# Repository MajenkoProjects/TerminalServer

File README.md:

Open-source Terminal Server
===========================

This is a small 6 port serial terminal server with ethernet, USB and WiFi
connectivity.

**NOTE: THIS IS WORK IN PROGRESS AND NOT COMPLETE YET**

Current status:
---------------

* **Serial Ports:** Done
* **USB Ports:** Done
* **Ethernet:** Done
* **WiFi:** Done
* **Telnet in:** Done
* **Telnet out:** Done
* **TCP in:** Done
* **TU58 Emulation:** Read/write done
* **TCP out:** Planned
* **PPP/SLIP:** Planned

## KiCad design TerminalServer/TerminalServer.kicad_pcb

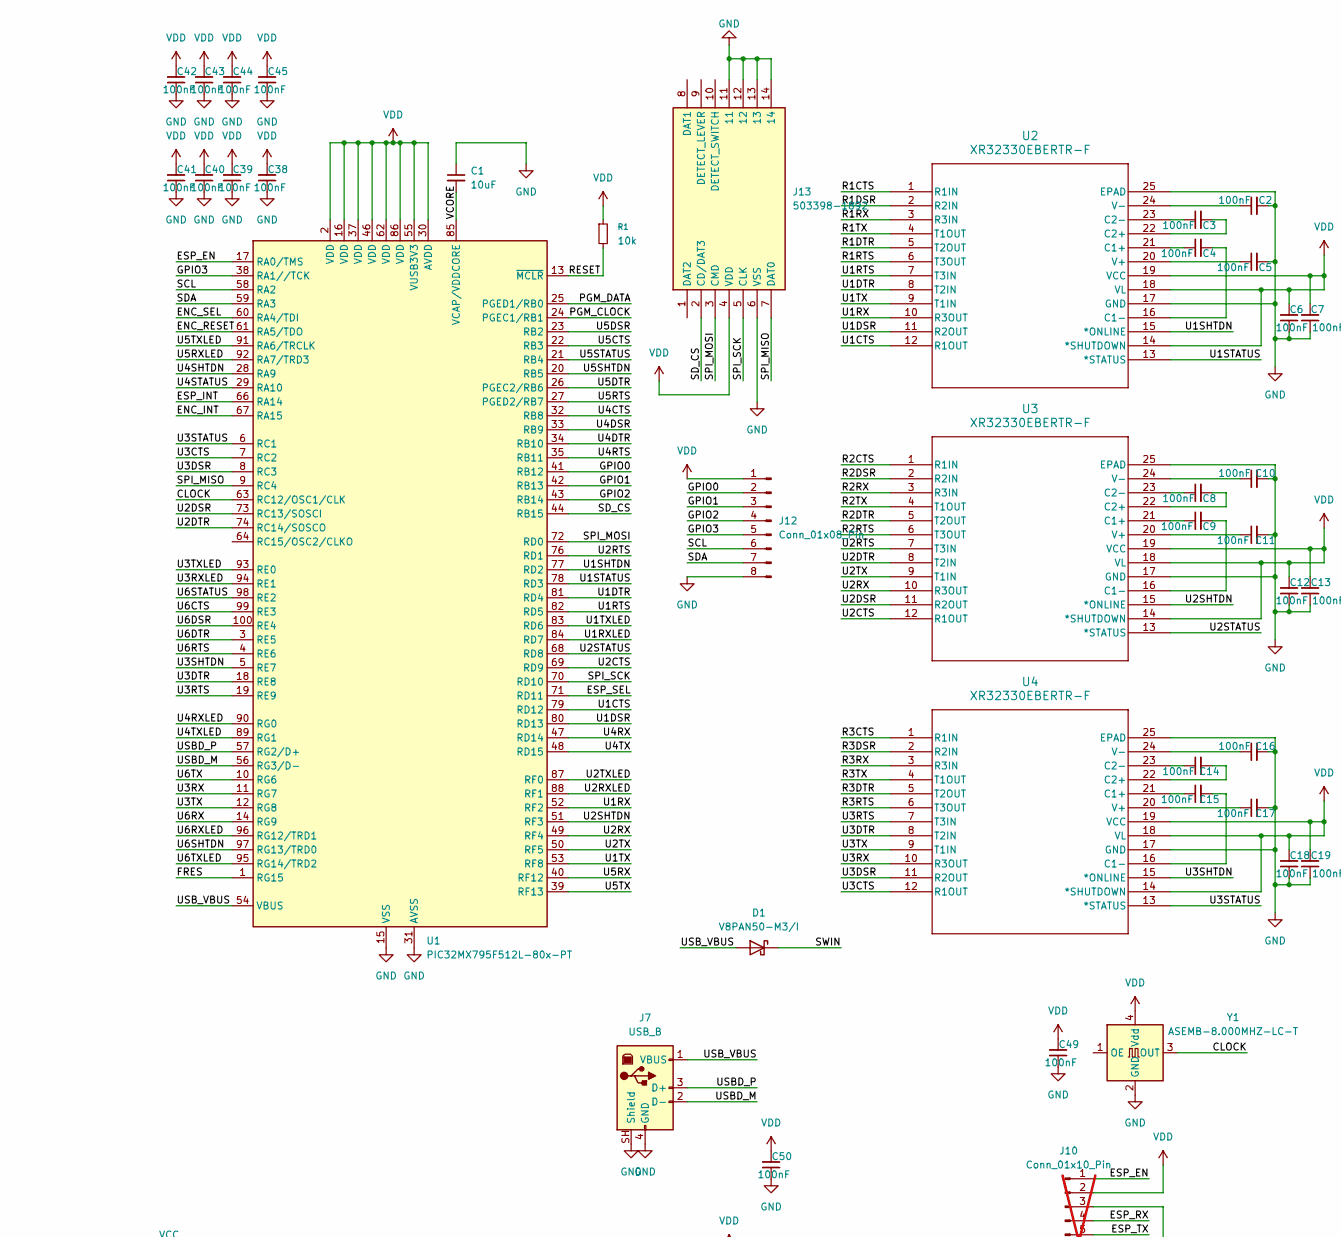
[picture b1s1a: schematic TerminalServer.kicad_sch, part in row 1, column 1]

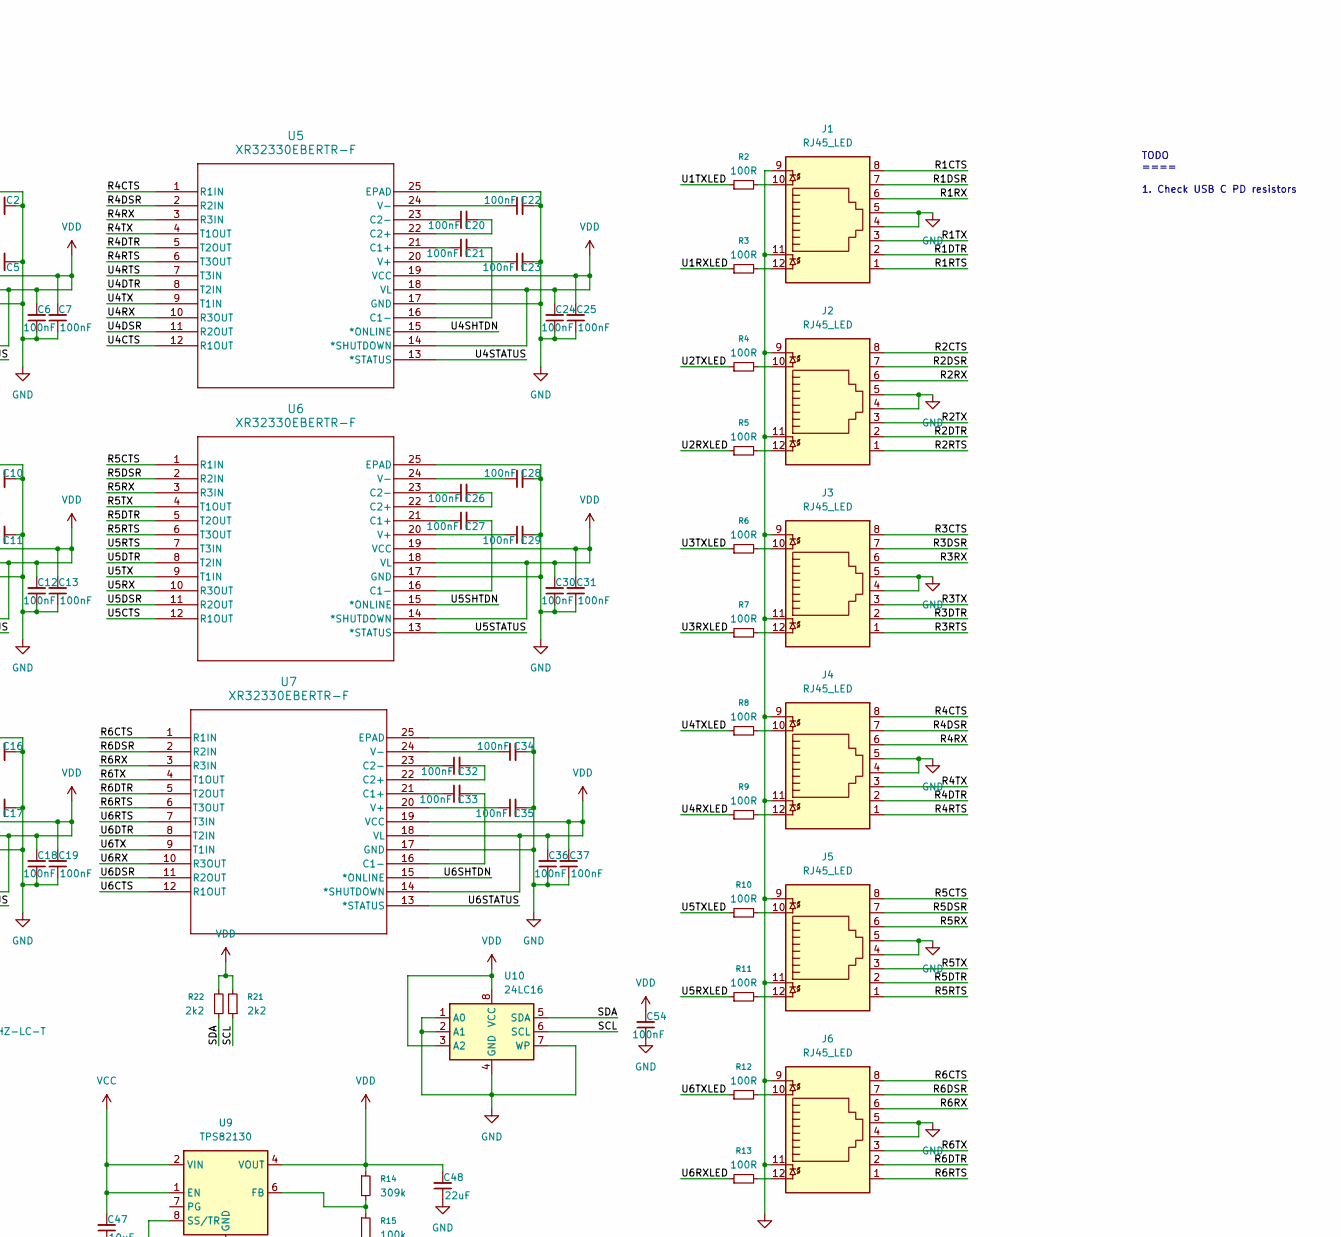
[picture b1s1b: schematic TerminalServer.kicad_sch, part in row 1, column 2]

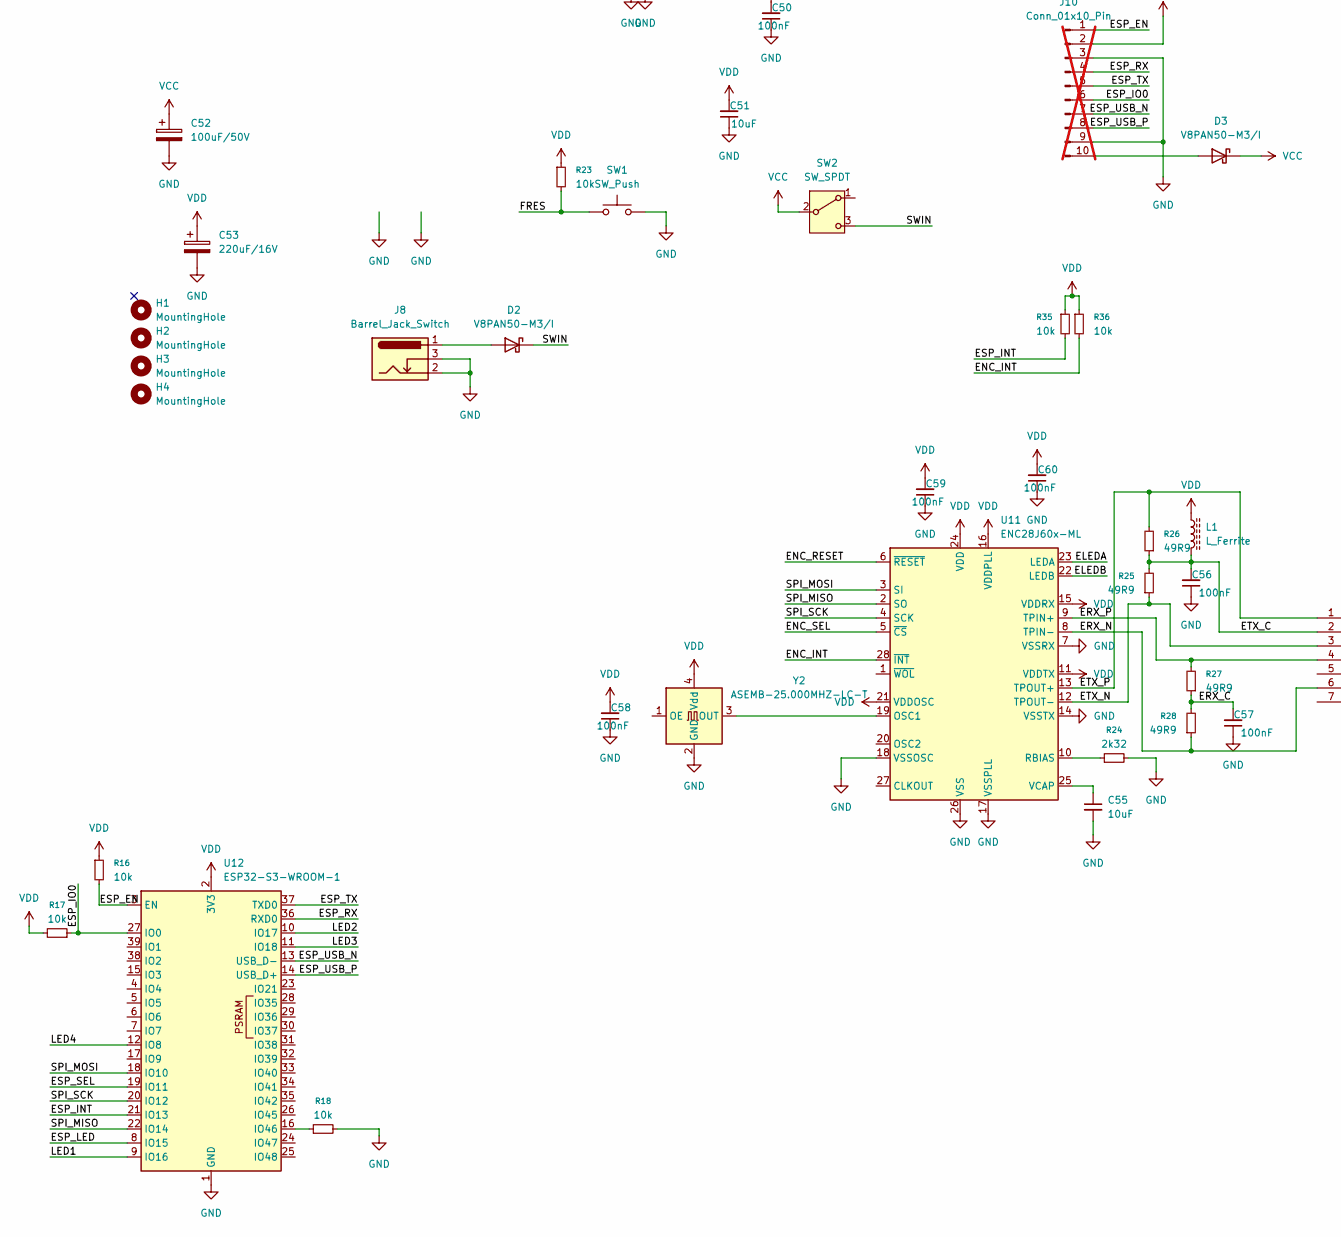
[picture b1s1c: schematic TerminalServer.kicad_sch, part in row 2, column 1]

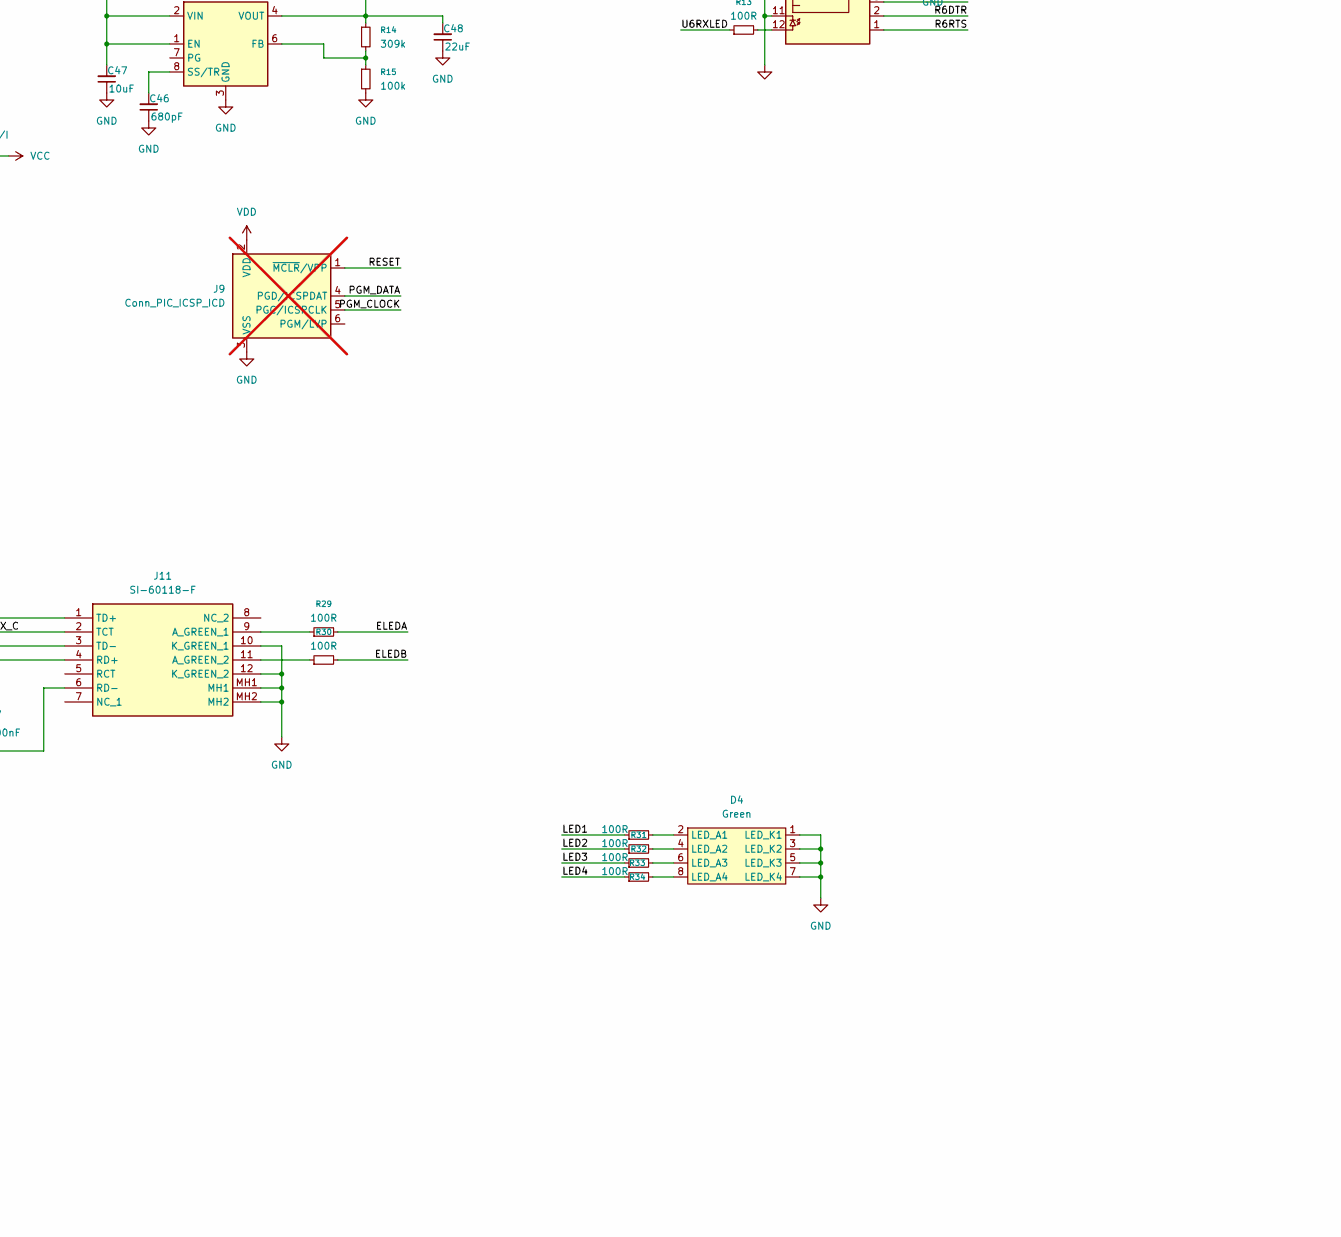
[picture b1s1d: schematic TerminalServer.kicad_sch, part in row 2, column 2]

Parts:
C1, C55: 10uF; C_0805_2012Metric_Pad1.18x1.45mm_HandSolder
C2, C3, C4, C5, C6, C7, C8, C9, C10, C11, C12, C13, C14, C15, C16, C17, C18, C19, C20, C21, C22, C23, C24, C25, C26, C27, C28, C29, C30, C31, C32, C33, C34, C35, C36, C37, C38, C39, C40, C41, C42, C43, C44, C45, C49, C50, C54, C56, C57, C58, C59, C60: 100nF; C_0603_1608Metric_Pad1.08x0.95mm_HandSolder
C46: 680pF; C_0603_1608Metric_Pad1.08x0.95mm_HandSolder
C47, C51: 10uF; C_1206_3216Metric
C48: 22uF; C_1206_3216Metric
C52: 100uF/50V; CP_Radial_D8.0mm_P3.50mm; Part ESK107M050AG3AA
C53: 220uF/16V; CP_Radial_D6.3mm_P2.50mm; Part ESK227M016AE3EA
D1, D2, D3: V8PAN50-M3/I; Vishay_SMPA; Mouser 78-V8PAN50-M3/I
D4: Green; XL-DZ234SYGD-4; Mouser 604-WP914CK4GDT
H1, H2, H3, H4: MountingHole; MountingHole_3.2mm_M3
J1, J2, J3, J4, J5, J6: RJ45_LED; RJ45_MTJ-88ARX1-LH_ADM; Mouser 737-MTJ-88ARX1-LH
J7: USB_B; USB_B_OST_USB-B1HSxx_Horizontal; Mouser 200-USBBSFBTHFR
J8: Barrel_Jack_Switch; BarrelJack_Wuerth_6941xx301002; Mouser 710-694106301002
J9: Conn_PIC_ICSP_ICD; PinHeader_1x06_P2.54mm_Vertical; not fitted
J10: Conn_01x10_Pin; PinHeader_1x10_P2.54mm_Vertical; not fitted
J11: SI-60118-F; SI60118F; Mouser Part Number 530-SI-60118-F
J12: Conn_01x08_Pin; PinHeader_1x08_P2.54mm_Vertical
J13: 503398-1892; 5033981892; Mouser Part Number 538-503398-1892
L1: L_Ferrite; L_0603_1608Metric_Pad1.05x0.95mm_HandSolder
R1, R16, R17, R18, R23, R35, R36: 10k; R_0603_1608Metric_Pad0.98x0.95mm_HandSolder
R2, R3, R4, R5, R6, R7, R8, R9, R10, R11, R12, R13, R29, R30, R31, R32, R33, R34: 100R; R_0603_1608Metric_Pad0.98x0.95mm_HandSolder
R14: 309k; R_0603_1608Metric_Pad0.98x0.95mm_HandSolder
R15: 100k; R_0603_1608Metric_Pad0.98x0.95mm_HandSolder
R21, R22: 2k2; R_0603_1608Metric_Pad0.98x0.95mm_HandSolder
R24: 2k32; R_0603_1608Metric_Pad0.98x0.95mm_HandSolder
R25, R26, R27, R28: 49R9; R_0603_1608Metric_Pad0.98x0.95mm_HandSolder
SW1: SW_Push; SW_Tactile_SPST_Angled_PTS645Vx31-2LFS
SW2: SW_SPDT; 34ASP23B4M7RT
U1: PIC32MX795F512L-80x-PT; TQFP-100_12x12mm_P0.4mm; Mouser 579-PIC32MX795F512
U2, U3, U4, U5, U6, U7: XR32330EBERTR-F; QFN-24; Mouser 701-XR32330EBERTR-F
U9: TPS82130; Texas_SIL0008D_MicroSiP-8-1EP_2.8x3mm_P0.65mm_EP1.1x1.9mm_T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
U10: 24LC16; SOIC-8_3.9x4.9mm_P1.27mm
U11: ENC28J60x-ML; QFN-28-1EP_6x6mm_P0.65mm_EP4.25x4.25mm
U12: ESP32-S3-WROOM-1
Y1: ASEMB-8.000MHZ-LC-T; Oscillator_SMD_SiT_PQFN-4Pin_3.2x2.5mm
Y2: ASEMB-25.000MHZ-LC-T; Oscillator_SMD_SiT_PQFN-4Pin_3.2x2.5mm

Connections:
/CLOCK: U1.63 (RC12/OSC1/CLK), Y1.3 (OUT)
/ELEDA: R29.2, U11.23 (LEDA)
/ELEDB: R30.2, U11.22 (LEDB)
/ENC_INT: R36.2, U1.67 (RA15), U11.28 (~INT)
/ENC_RESET: U1.61 (RA5/TDO), U11.6 (~RESET)
/ENC_SEL: U1.60 (RA4/TDI), U11.5 (~CS)
/ERX_C: C57.2, R27.1, R28.2
/ERX_N: J11.6 (RD-), R28.1, U11.8 (TPIN-)
/ERX_P: J11.4 (RD+), R27.2, U11.9 (TPIN+)
/ESP_EN: J10.1, R16.2, U1.17 (RA0/TMS), U12.3 (EN)
/ESP_INT: R35.2, U1.66 (RA14), U12.21 (IO13)
/ESP_IO0: J10.6, R17.1, U12.27 (IO0)
/ESP_LED: U12.8 (IO15)
/ESP_RX: J10.4, U12.36 (RXD0)
/ESP_SEL: U1.71 (RD11), U12.19 (IO11)
/ESP_TX: J10.5, U12.37 (TXD0)
/ESP_USB_N: J10.7, U12.13 (USB_D-)
/ESP_USB_P: J10.8, U12.14 (USB_D+)
/ETX_C: C56.2, J11.2 (TCT), L1.2, R25.2, R26.1
/ETX_N: J11.3 (TD-), R25.1, U11.12 (TPOUT-)
/ETX_P: J11.1 (TD+), R26.2, U11.13 (TPOUT+)
/FRES: R23.2, SW1.1, U1.1 (RG15)
/GPIO0: J12.2, U1.41 (RB12)
/GPIO1: J12.3, U1.42 (RB13)
/GPIO2: J12.4, U1.43 (RB14)
/GPIO3: J12.5, U1.38 (RA1//TCK)
/LED1: R31.1, U12.9 (IO16)
/LED2: R32.1, U12.10 (IO17)
/LED3: R33.1, U12.11 (IO18)
/LED4: R34.1, U12.12 (IO8)
/PGM_CLOCK: J9.5 (PGC/ICSPCLK), U1.24 (PGEC1/RB1)
/PGM_DATA: J9.4 (PGD/ICSPDAT), U1.25 (PGED1/RB0)
/R1CTS: J1.8, U2.1 (R1IN)
/R1DSR: J1.7, U2.2 (R2IN)
/R1DTR: J1.2, U2.5 (T2OUT)
/R1RTS: J1.1, U2.6 (T3OUT)
/R1RX: J1.6, U2.3 (R3IN)
/R1TX: J1.3, U2.4 (T1OUT)
/R2CTS: J2.8, U3.1 (R1IN)
/R2DSR: J2.7, U3.2 (R2IN)
/R2DTR: J2.2, U3.5 (T2OUT)
/R2RTS: J2.1, U3.6 (T3OUT)
/R2RX: J2.6, U3.3 (R3IN)
/R2TX: J2.3, U3.4 (T1OUT)
/R3CTS: J3.8, U4.1 (R1IN)
/R3DSR: J3.7, U4.2 (R2IN)
/R3DTR: J3.2, U4.5 (T2OUT)
/R3RTS: J3.1, U4.6 (T3OUT)
/R3RX: J3.6, U4.3 (R3IN)
/R3TX: J3.3, U4.4 (T1OUT)
/R4CTS: J4.8, U5.1 (R1IN)
/R4DSR: J4.7, U5.2 (R2IN)
/R4DTR: J4.2, U5.5 (T2OUT)
/R4RTS: J4.1, U5.6 (T3OUT)
/R4RX: J4.6, U5.3 (R3IN)
/R4TX: J4.3, U5.4 (T1OUT)
/R5CTS: J5.8, U6.1 (R1IN)
/R5DSR: J5.7, U6.2 (R2IN)
/R5DTR: J5.2, U6.5 (T2OUT)
/R5RTS: J5.1, U6.6 (T3OUT)
/R5RX: J5.6, U6.3 (R3IN)
/R5TX: J5.3, U6.4 (T1OUT)
/R6CTS: J6.8, U7.1 (R1IN)
/R6DSR: J6.7, U7.2 (R2IN)
/R6DTR: J6.2, U7.5 (T2OUT)
/R6RTS: J6.1, U7.6 (T3OUT)
/R6RX: J6.6, U7.3 (R3IN)
/R6TX: J6.3, U7.4 (T1OUT)
/RESET: J9.1 (~MCLR/VPP), R1.2, U1.13 (~MCLR)
/SCL: J12.6, R21.1, U1.58 (RA2), U10.6 (SCL)
/SDA: J12.7, R22.1, U1.59 (RA3), U10.5 (SDA)
/SD_CS: J13.2 (CD/DAT3), U1.44 (RB15)
/SPI_MISO: J13.7 (DAT0), U1.9 (RC4), U11.2 (SO), U12.22 (IO14)
/SPI_MOSI: J13.3 (CMD), U1.72 (RD0), U11.3 (SI), U12.18 (IO10)
/SPI_SCK: J13.5 (CLK), U1.70 (RD10), U11.4 (SCK), U12.20 (IO12)
/SWIN: D1.1 (K), D2.1 (K), SW2.3 (C)
/U1CTS: U1.79 (RD12), U2.12 (R1OUT)
/U1DSR: U1.80 (RD13), U2.11 (R2OUT)
/U1DTR: U1.81 (RD4), U2.8 (T2IN)
/U1RTS: U1.82 (RD5), U2.7 (T3IN)
/U1RX: U1.52 (RF2), U2.10 (R3OUT)
/U1RXLED: R3.1, U1.84 (RD7)
/U1SHTDN: U1.77 (RD2), U2.15 (*ONLINE)
/U1STATUS: U1.78 (RD3), U2.13 (*STATUS)
/U1TX: U1.53 (RF8), U2.9 (T1IN)
/U1TXLED: R2.1, U1.83 (RD6)
/U2CTS: U1.69 (RD9), U3.12 (R1OUT)
/U2DSR: U1.73 (RC13/SOSCI), U3.11 (R2OUT)
/U2DTR: U1.74 (RC14/SOSCO), U3.8 (T2IN)
/U2RTS: U1.76 (RD1), U3.7 (T3IN)
/U2RX: U1.49 (RF4), U3.10 (R3OUT)
/U2RXLED: R5.1, U1.88 (RF1)
/U2SHTDN: U1.51 (RF3), U3.15 (*ONLINE)
/U2STATUS: U1.68 (RD8), U3.13 (*STATUS)
/U2TX: U1.50 (RF5), U3.9 (T1IN)
/U2TXLED: R4.1, U1.87 (RF0)
/U3CTS: U1.7 (RC2), U4.12 (R1OUT)
/U3DSR: U1.8 (RC3), U4.11 (R2OUT)
/U3DTR: U1.18 (RE8), U4.8 (T2IN)
/U3RTS: U1.19 (RE9), U4.7 (T3IN)
/U3RX: U1.11 (RG7), U4.10 (R3OUT)
/U3RXLED: R7.1, U1.94 (RE1)
/U3SHTDN: U1.5 (RE7), U4.15 (*ONLINE)
/U3STATUS: U1.6 (RC1), U4.13 (*STATUS)
/U3TX: U1.12 (RG8), U4.9 (T1IN)
/U3TXLED: R6.1, U1.93 (RE0)
/U4CTS: U1.32 (RB8), U5.12 (R1OUT)
/U4DSR: U1.33 (RB9), U5.11 (R2OUT)
/U4DTR: U1.34 (RB10), U5.8 (T2IN)
/U4RTS: U1.35 (RB11), U5.7 (T3IN)
/U4RX: U1.47 (RD14), U5.10 (R3OUT)
/U4RXLED: R9.1, U1.90 (RG0)
/U4SHTDN: U1.28 (RA9), U5.15 (*ONLINE)
/U4STATUS: U1.29 (RA10), U5.13 (*STATUS)
/U4TX: U1.48 (RD15), U5.9 (T1IN)
/U4TXLED: R8.1, U1.89 (RG1)
/U5CTS: U1.22 (RB3), U6.12 (R1OUT)
/U5DSR: U1.23 (RB2), U6.11 (R2OUT)
/U5DTR: U1.26 (PGEC2/RB6), U6.8 (T2IN)
/U5RTS: U1.27 (PGED2/RB7), U6.7 (T3IN)
/U5RX: U1.40 (RF12), U6.10 (R3OUT)
/U5RXLED: R11.1, U1.92 (RA7/TRD3)
/U5SHTDN: U1.20 (RB5), U6.15 (*ONLINE)
/U5STATUS: U1.21 (RB4), U6.13 (*STATUS)
/U5TX: U1.39 (RF13), U6.9 (T1IN)
/U5TXLED: R10.1, U1.91 (RA6/TRCLK)
/U6CTS: U1.99 (RE3), U7.12 (R1OUT)
/U6DSR: U1.100 (RE4), U7.11 (R2OUT)
/U6DTR: U1.3 (RE5), U7.8 (T2IN)
/U6RTS: U1.4 (RE6), U7.7 (T3IN)
/U6RX: U1.14 (RG9), U7.10 (R3OUT)
/U6RXLED: R13.1, U1.96 (RG12/TRD1)
/U6SHTDN: U1.97 (RG13/TRD0), U7.15 (*ONLINE)
/U6STATUS: U1.98 (RE2), U7.13 (*STATUS)
/U6TX: U1.10 (RG6), U7.9 (T1IN)
/U6TXLED: R12.1, U1.95 (RG14/TRD2)
/USBD_M: J7.2 (D-), U1.56 (RG3/D-)
/USBD_P: J7.3 (D+), U1.57 (RG2/D+)
/USB_VBUS: D1.2 (A), J7.1 (VBUS), U1.54 (VBUS)
/VCORE: C1.2, U1.85 (VCAP/VDDCORE)
GND: C1.1, C2.2, C5.2, C6.1, C7.1, C10.2, C11.2, C12.1, C13.1, C16.2, C17.2, C18.1, C19.1, C22.2, C23.2, C24.1, C25.1, C28.2, C29.2, C30.1, C31.1, C34.2, C35.2, C36.1, C37.1, C38.1, C39.1, C40.1, C41.1, C42.1, C43.1, C44.1, C45.1, C46.1, C47.1, C48.1, C49.1, C50.1, C51.1, C52.2, C53.2, C54.1, C55.2, C56.1, C57.1, C58.1, C59.1, C60.1, D4.1 (LED_K1), D4.3 (LED_K2), D4.5 (LED_K3), D4.7 (LED_K4), J1.4, J1.5, J1.9, J1.11, J2.4, J2.5, J2.9, J2.11, J3.4, J3.5, J3.9, J3.11, J4.4, J4.5, J4.9, J4.11, J5.4, J5.5, J5.9, J5.11, J6.4, J6.5, J6.9, J6.11, J7.4 (GND), J7.SH (Shield), J8.2, J8.3, J9.3 (VSS), J10.3, J10.9, J11.10 (K_GREEN_1), J11.12 (K_GREEN_2), J11.MH1, J11.MH2, J12.8, J13.6 (VSS), J13.11, J13.12, J13.13, J13.14, R15.2, R18.2, R24.2, SW1.2, U1.15 (VSS), U1.31 (AVSS), U1.36 (VSS), U1.45 (VSS), U1.65 (VSS), U1.75 (VSS), U2.17 (GND), U2.25 (EPAD), U3.17 (GND), U3.25 (EPAD), U4.17 (GND), U4.25 (EPAD), U5.17 (GND), U5.25 (EPAD), U6.17 (GND), U6.25 (EPAD), U7.17 (GND), U7.25 (EPAD), U9.3 (GND), U9.9 (GND), U10.1 (A0), U10.2 (A1), U10.4 (GND), U10.7 (WP), U11.7 (VSSRX), U11.14 (VSSTX), U11.17 (VSSPLL), U11.18 (VSSOSC), U11.26 (VSS), U12.1 (GND), U12.40 (GND), U12.41 (GND), Y1.2 (GND), Y2.2 (GND)
unnamed: D2.2 (A), J8.1
unnamed: D3.2 (A), J10.10
unnamed: D4.2 (LED_A1), R31.2
unnamed: D4.4 (LED_A2), R32.2
unnamed: D4.6 (LED_A3), R33.2
unnamed: D4.8 (LED_A4), R34.2
unnamed: J1.10, R2.2
unnamed: J1.12, R3.2
unnamed: J2.10, R4.2
unnamed: J2.12, R5.2
unnamed: J3.10, R6.2
unnamed: J3.12, R7.2
unnamed: J4.10, R8.2
unnamed: J4.12, R9.2
unnamed: J5.10, R10.2
unnamed: J5.12, R11.2
unnamed: J6.10, R12.2
unnamed: J6.12, R13.2
unnamed: J11.9 (A_GREEN_1), R29.1
unnamed: J11.11 (A_GREEN_2), R30.1
unnamed: C4.1, U2.21 (C1+)
unnamed: C4.2, U2.16 (C1-)
unnamed: C3.2, U2.22 (C2+)
unnamed: C3.1, U2.23 (C2-)
unnamed: C5.1, U2.20 (V+)
unnamed: C2.1, U2.24 (V-)
unnamed: C9.1, U3.21 (C1+)
unnamed: C9.2, U3.16 (C1-)
unnamed: C8.2, U3.22 (C2+)
unnamed: C8.1, U3.23 (C2-)
unnamed: C11.1, U3.20 (V+)
unnamed: C10.1, U3.24 (V-)
unnamed: C15.1, U4.21 (C1+)
unnamed: C15.2, U4.16 (C1-)
unnamed: C14.2, U4.22 (C2+)
unnamed: C14.1, U4.23 (C2-)
unnamed: C17.1, U4.20 (V+)
unnamed: C16.1, U4.24 (V-)
unnamed: C21.1, U5.21 (C1+)
unnamed: C21.2, U5.16 (C1-)
unnamed: C20.2, U5.22 (C2+)
unnamed: C20.1, U5.23 (C2-)
unnamed: C23.1, U5.20 (V+)
unnamed: C22.1, U5.24 (V-)
unnamed: C27.1, U6.21 (C1+)
unnamed: C27.2, U6.16 (C1-)
unnamed: C26.2, U6.22 (C2+)
unnamed: C26.1, U6.23 (C2-)
unnamed: C29.1, U6.20 (V+)
unnamed: C28.1, U6.24 (V-)
unnamed: C33.1, U7.21 (C1+)
unnamed: C33.2, U7.16 (C1-)
unnamed: C32.2, U7.22 (C2+)
unnamed: C32.1, U7.23 (C2-)
unnamed: C35.1, U7.20 (V+)
unnamed: C34.1, U7.24 (V-)
unnamed: R14.2, R15.1, U9.6 (FB)
unnamed: C46.2, U9.8 (SS/TR)
unnamed: U11.19 (OSC1), Y2.3 (OUT)
unnamed: R24.1, U11.10 (RBIAS)
unnamed: C55.1, U11.25 (VCAP)
unnamed: R18.1, U12.16 (IO46)
VCC: C47.2, C52.1, D3.1 (K), SW2.2 (B), U9.1 (EN), U9.2 (VIN)
VDD: C6.2, C7.2, C12.2, C13.2, C18.2, C19.2, C24.2, C25.2, C30.2, C31.2, C36.2, C37.2, C38.2, C39.2, C40.2, C41.2, C42.2, C43.2, C44.2, C45.2, C48.2, C49.2, C50.2, C51.2, C53.1, C54.2, C58.2, C59.2, C60.2, J9.2 (VDD), J10.2, J12.1, J13.4 (VDD), L1.1, R1.1, R14.1, R16.1, R17.2, R21.2, R22.2, R23.1, R35.1, R36.1, U1.2 (VDD), U1.16 (VDD), U1.30 (AVDD), U1.37 (VDD), U1.46 (VDD), U1.55 (VUSB3V3), U1.62 (VDD), U1.86 (VDD), U2.14 (*SHUTDOWN), U2.18 (VL), U2.19 (VCC), U3.14 (*SHUTDOWN), U3.18 (VL), U3.19 (VCC), U4.14 (*SHUTDOWN), U4.18 (VL), U4.19 (VCC), U5.14 (*SHUTDOWN), U5.18 (VL), U5.19 (VCC), U6.14 (*SHUTDOWN), U6.18 (VL), U6.19 (VCC), U7.14 (*SHUTDOWN), U7.18 (VL), U7.19 (VCC), U9.4 (VOUT), U9.5 (VOUT), U10.3 (A2), U10.8 (VCC), U11.11 (VDDTX), U11.15 (VDDRX), U11.16 (VDDPLL), U11.21 (VDDOSC), U11.24 (VDD), U12.2 (3V3), Y1.4 (Vdd), Y2.4 (Vdd)

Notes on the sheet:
TODO ==== 1. Check USB C PD resistors

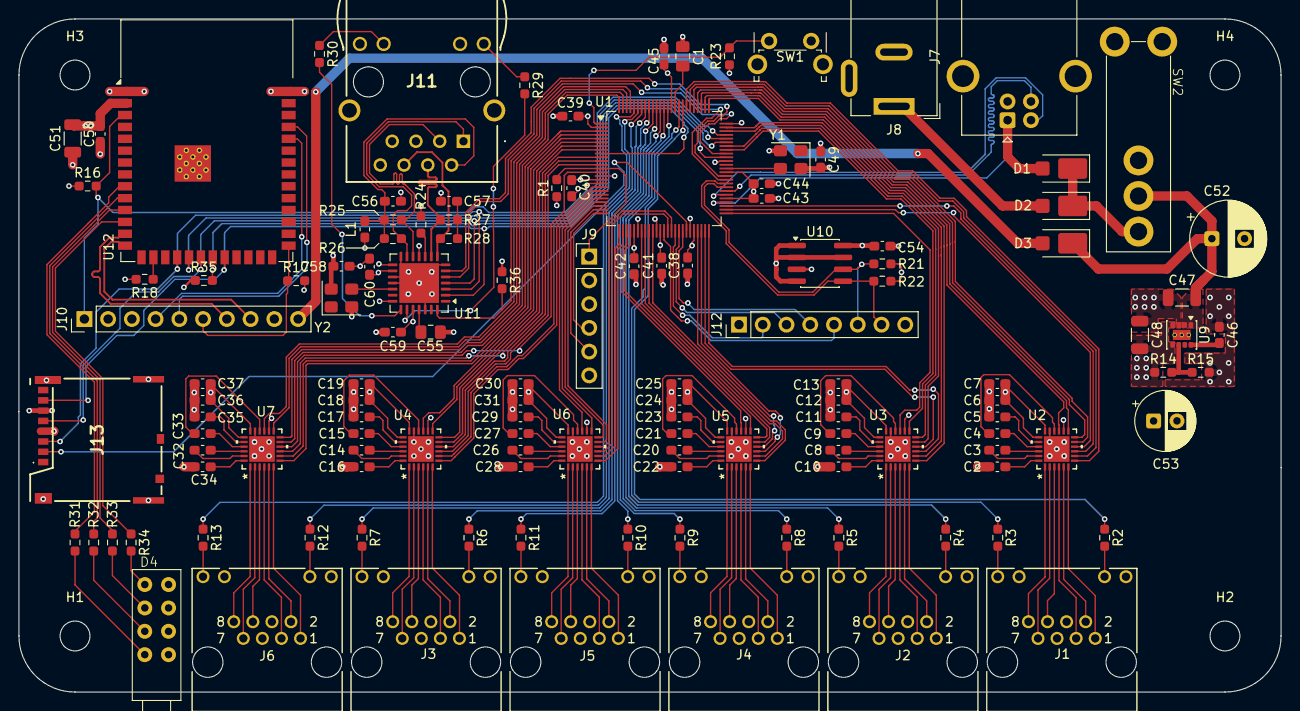
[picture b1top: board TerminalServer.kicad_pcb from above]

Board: 4 copper layers, 135.0 x 72.0 mm, 131 parts (0 on the bottom side), 204 nets.

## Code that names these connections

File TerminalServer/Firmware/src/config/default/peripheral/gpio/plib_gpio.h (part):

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// *****************************************************************************


/*** Macros for FRES pin ***/
#define FRES_Set()               (LATGSET = (1<<15))
#define FRES_Clear()             (LATGCLR = (1<<15))
#define FRES_Toggle()            (LATGINV= (1<<15))
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#define FRES_InputEnable()       (TRISGSET = (1<<15))
#define FRES_Get()               ((PORTG >> 15) & 0x1)
#define FRES_GetLatch()          ((LATG >> 15) & 0x1)
#define FRES_PIN                  GPIO_PIN_RG15

/*** Macros for U6DTR pin ***/
#define U6DTR_Set()               (LATESET = (1<<5))
#define U6DTR_Clear()             (LATECLR = (1<<5))
#define U6DTR_Toggle()            (LATEINV= (1<<5))
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#define U6DTR_InputEnable()       (TRISESET = (1<<5))
#define U6DTR_Get()               ((PORTE >> 5) & 0x1)
#define U6DTR_GetLatch()          ((LATE >> 5) & 0x1)
#define U6DTR_PIN                  GPIO_PIN_RE5

/*** Macros for U6RTS pin ***/
#define U6RTS_Set()               (LATESET = (1<<6))
#define U6RTS_Clear()             (LATECLR = (1<<6))
#define U6RTS_Toggle()            (LATEINV= (1<<6))
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#define U6RTS_InputEnable()       (TRISESET = (1<<6))
#define U6RTS_Get()               ((PORTE >> 6) & 0x1)
#define U6RTS_GetLatch()          ((LATE >> 6) & 0x1)
#define U6RTS_PIN                  GPIO_PIN_RE6

/*** Macros for U3SHTDN pin ***/
#define U3SHTDN_Set()               (LATESET = (1<<7))
#define U3SHTDN_Clear()             (LATECLR = (1<<7))
#define U3SHTDN_Toggle()            (LATEINV= (1<<7))
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#define U3SHTDN_InputEnable()       (TRISESET = (1<<7))
#define U3SHTDN_Get()               ((PORTE >> 7) & 0x1)
#define U3SHTDN_GetLatch()          ((LATE >> 7) & 0x1)
#define U3SHTDN_PIN                  GPIO_PIN_RE7

/*** Macros for U3STATUS pin ***/
#define U3STATUS_Set()               (LATCSET = (1<<1))
#define U3STATUS_Clear()             (LATCCLR = (1<<1))
#define U3STATUS_Toggle()            (LATCINV= (1<<1))
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#define U3STATUS_InputEnable()       (TRISCSET = (1<<1))
#define U3STATUS_Get()               ((PORTC >> 1) & 0x1)
#define U3STATUS_GetLatch()          ((LATC >> 1) & 0x1)
#define U3STATUS_PIN                  GPIO_PIN_RC1

/*** Macros for U3CTS pin ***/
#define U3CTS_Set()               (LATCSET = (1<<2))
#define U3CTS_Clear()             (LATCCLR = (1<<2))
#define U3CTS_Toggle()            (LATCINV= (1<<2))
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#define U3CTS_InputEnable()       (TRISCSET = (1<<2))
#define U3CTS_Get()               ((PORTC >> 2) & 0x1)
#define U3CTS_GetLatch()          ((LATC >> 2) & 0x1)
#define U3CTS_PIN                  GPIO_PIN_RC2

/*** Macros for U3DSR pin ***/
#define U3DSR_Set()               (LATCSET = (1<<3))
#define U3DSR_Clear()             (LATCCLR = (1<<3))
#define U3DSR_Toggle()            (LATCINV= (1<<3))
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#define U3DSR_InputEnable()       (TRISCSET = (1<<3))
#define U3DSR_Get()               ((PORTC >> 3) & 0x1)
#define U3DSR_GetLatch()          ((LATC >> 3) & 0x1)
#define U3DSR_PIN                  GPIO_PIN_RC3

/*** Macros for SDI_MISO pin ***/
#define SDI_MISO_Get()               ((PORTC >> 4) & 0x1)
#define SDI_MISO_GetLatch()          ((LATC >> 4) & 0x1)
#define SDI_MISO_PIN                  GPIO_PIN_RC4

/*** Macros for U6TX pin ***/
#define U6TX_Get()               ((PORTG >> 6) & 0x1)
#define U6TX_GetLatch()          ((LATG >> 6) & 0x1)
#define U6TX_PIN                  GPIO_PIN_RG6

/*** Macros for U3RX pin ***/
#define U3RX_Get()               ((PORTG >> 7) & 0x1)
#define U3RX_GetLatch()          ((LATG >> 7) & 0x1)
#define U3RX_PIN                  GPIO_PIN_RG7

/*** Macros for U3TX pin ***/
#define U3TX_Get()               ((PORTG >> 8) & 0x1)
#define U3TX_GetLatch()          ((LATG >> 8) & 0x1)
#define U3TX_PIN                  GPIO_PIN_RG8

/*** Macros for U6RX pin ***/
#define U6RX_Get()               ((PORTG >> 9) & 0x1)
#define U6RX_GetLatch()          ((LATG >> 9) & 0x1)
#define U6RX_PIN                  GPIO_PIN_RG9

/*** Macros for ESP_EN pin ***/
#define ESP_EN_Set()               (LATASET = (1<<0))
#define ESP_EN_Clear()             (LATACLR = (1<<0))
#define ESP_EN_Toggle()            (LATAINV= (1<<0))
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#define ESP_EN_InputEnable()       (TRISASET = (1<<0))
#define ESP_EN_Get()               ((PORTA >> 0) & 0x1)
#define ESP_EN_GetLatch()          ((LATA >> 0) & 0x1)
#define ESP_EN_PIN                  GPIO_PIN_RA0

/*** Macros for U3DTR pin ***/
#define U3DTR_Set()               (LATESET = (1<<8))
#define U3DTR_Clear()             (LATECLR = (1<<8))
#define U3DTR_Toggle()            (LATEINV= (1<<8))
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#define U3DTR_InputEnable()       (TRISESET = (1<<8))
#define U3DTR_Get()               ((PORTE >> 8) & 0x1)
#define U3DTR_GetLatch()          ((LATE >> 8) & 0x1)
#define U3DTR_PIN                  GPIO_PIN_RE8

/*** Macros for U3RTS pin ***/
#define U3RTS_Set()               (LATESET = (1<<9))
#define U3RTS_Clear()             (LATECLR = (1<<9))
#define U3RTS_Toggle()            (LATEINV= (1<<9))
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#define U3RTS_InputEnable()       (TRISESET = (1<<9))
#define U3RTS_Get()               ((PORTE >> 9) & 0x1)
#define U3RTS_GetLatch()          ((LATE >> 9) & 0x1)
#define U3RTS_PIN                  GPIO_PIN_RE9

/*** Macros for U5SHTDN pin ***/
#define U5SHTDN_Set()               (LATBSET = (1<<5))
#define U5SHTDN_Clear()             (LATBCLR = (1<<5))
#define U5SHTDN_Toggle()            (LATBINV= (1<<5))
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#define U5SHTDN_InputEnable()       (TRISBSET = (1<<5))
#define U5SHTDN_Get()               ((PORTB >> 5) & 0x1)
#define U5SHTDN_GetLatch()          ((LATB >> 5) & 0x1)
#define U5SHTDN_PIN                  GPIO_PIN_RB5

/*** Macros for U5STATUS pin ***/
#define U5STATUS_Set()               (LATBSET = (1<<4))
#define U5STATUS_Clear()             (LATBCLR = (1<<4))
#define U5STATUS_Toggle()            (LATBINV= (1<<4))
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#define U5STATUS_InputEnable()       (TRISBSET = (1<<4))
#define U5STATUS_Get()               ((PORTB >> 4) & 0x1)
#define U5STATUS_GetLatch()          ((LATB >> 4) & 0x1)
#define U5STATUS_PIN                  GPIO_PIN_RB4

/*** Macros for U5CTS pin ***/
#define U5CTS_Set()               (LATBSET = (1<<3))
#define U5CTS_Clear()             (LATBCLR = (1<<3))
#define U5CTS_Toggle()            (LATBINV= (1<<3))
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#define U5CTS_InputEnable()       (TRISBSET = (1<<3))
#define U5CTS_Get()               ((PORTB >> 3) & 0x1)
#define U5CTS_GetLatch()          ((LATB >> 3) & 0x1)
#define U5CTS_PIN                  GPIO_PIN_RB3

/*** Macros for U5DSR pin ***/
#define U5DSR_Set()               (LATBSET = (1<<2))
#define U5DSR_Clear()             (LATBCLR = (1<<2))
#define U5DSR_Toggle()            (LATBINV= (1<<2))
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#define U5DSR_InputEnable()       (TRISBSET = (1<<2))
#define U5DSR_Get()               ((PORTB >> 2) & 0x1)
#define U5DSR_GetLatch()          ((LATB >> 2) & 0x1)
#define U5DSR_PIN                  GPIO_PIN_RB2

/*** Macros for PGM_CLOCK pin ***/
#define PGM_CLOCK_Set()               (LATBSET = (1<<1))
#define PGM_CLOCK_Clear()             (LATBCLR = (1<<1))
#define PGM_CLOCK_Toggle()            (LATBINV= (1<<1))
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#define PGM_CLOCK_InputEnable()       (TRISBSET = (1<<1))
#define PGM_CLOCK_Get()               ((PORTB >> 1) & 0x1)
#define PGM_CLOCK_GetLatch()          ((LATB >> 1) & 0x1)
#define PGM_CLOCK_PIN                  GPIO_PIN_RB1

/*** Macros for PGM_DATA pin ***/
#define PGM_DATA_Set()               (LATBSET = (1<<0))
#define PGM_DATA_Clear()             (LATBCLR = (1<<0))
#define PGM_DATA_Toggle()            (LATBINV= (1<<0))
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#define PGM_DATA_InputEnable()       (TRISBSET = (1<<0))
#define PGM_DATA_Get()               ((PORTB >> 0) & 0x1)
#define PGM_DATA_GetLatch()          ((LATB >> 0) & 0x1)
#define PGM_DATA_PIN                  GPIO_PIN_RB0

/*** Macros for U5DTR pin ***/
#define U5DTR_Set()               (LATBSET = (1<<6))
#define U5DTR_Clear()             (LATBCLR = (1<<6))
#define U5DTR_Toggle()            (LATBINV= (1<<6))
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#define U5DTR_InputEnable()       (TRISBSET = (1<<6))
#define U5DTR_Get()               ((PORTB >> 6) & 0x1)
#define U5DTR_GetLatch()          ((LATB >> 6) & 0x1)
#define U5DTR_PIN                  GPIO_PIN_RB6

/*** Macros for U5RTS pin ***/
#define U5RTS_Set()               (LATBSET = (1<<7))
#define U5RTS_Clear()             (LATBCLR = (1<<7))
#define U5RTS_Toggle()            (LATBINV= (1<<7))
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#define U5RTS_InputEnable()       (TRISBSET = (1<<7))
#define U5RTS_Get()               ((PORTB >> 7) & 0x1)
#define U5RTS_GetLatch()          ((LATB >> 7) & 0x1)
#define U5RTS_PIN                  GPIO_PIN_RB7

/*** Macros for U4SHTDN pin ***/
#define U4SHTDN_Set()               (LATASET = (1<<9))
#define U4SHTDN_Clear()             (LATACLR = (1<<9))
#define U4SHTDN_Toggle()            (LATAINV= (1<<9))
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#define U4SHTDN_InputEnable()       (TRISASET = (1<<9))
#define U4SHTDN_Get()               ((PORTA >> 9) & 0x1)
#define U4SHTDN_GetLatch()          ((LATA >> 9) & 0x1)
#define U4SHTDN_PIN                  GPIO_PIN_RA9

/*** Macros for U4STATUS pin ***/
#define U4STATUS_Set()               (LATASET = (1<<10))
#define U4STATUS_Clear()             (LATACLR = (1<<10))
#define U4STATUS_Toggle()            (LATAINV= (1<<10))
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
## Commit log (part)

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2026-02-07 Initial import
2026-02-09 Progress
2026-02-24 Almost complete
2026-02-26 Added Ethernet and more
2026-02-27 Added 4-led module
2026-03-01 Improved render interface
2026-03-05 Added readme
2026-03-07 Updated picture
2026-05-15 Added SD card
2026-05-28 Final cleanup
2026-05-29 Reverted to quad LED

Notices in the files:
TerminalServer/Firmware/src/config/default/peripheral/gpio/plib_gpio.h:
Copyright (C) 2019 Microchip Technology Inc. and its subsidiaries.
